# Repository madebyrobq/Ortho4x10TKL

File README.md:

# Ortho 4x10 TKL v0.1

### Summary

An open-source custom mechanical keyboard featuring
* 4x10 ortholinear 'tenkeyless' style layout
* Raspberry Pi RP2040 integrated microcontroller
* USB-C
* Hotswap sockets
* Fully factory-assembled PCBA
* QMK Vial firmware

### Goals

The goals of this project were:
1. Learn how to make a working PCBA mechanical keyboard
2. Keep hardware features to the minimum (no LEDs, OLED, encoders, etc.)
3. Fun and delighful > practical
4. Companion for iPad Mini (6th gen)

### Layout

Spacebar cluster supports 3x1U and 1x3U layouts. Stabilizers are not currently supported but can be substituted with loose switches if desired.

Arrow cluster supports 4 or 6 keys, although the top cases in this repo will cover up 2 of them. Still, the switches are there if you prefer to have them.

### Keymap

This is my keymap, note that with VIAL firmware some setup will be manual in the VIAL application or loaded from a saved layout

```
Default Layer:
┌───────┬───────┬───────┬───────┬───────┬───────┬───────┐┌───────┬───────┬───────┐
│   Q (TAB) W   │   E   │   R   │   T   │   Y   │   U   ││   I   │   O (DEL) P   │
└───────┴───────┴───────┴───────┴───────┴───────┴───────┘├───────┼───────┼───────┤
┌───────┬───────┬───────┬───────┬───────┬───────┬───────┐│   K   │   L (ENT) ;   │
│   A (ESC) S   │   D   │   F   │   G   │   H   │   J   │└───────┴───────┴───────┘
├───────┼───────┼───────┼───────┼───────┼───────┼───────┤┌       ┌───────┐       ┐
│  Z(⇧) │   X   │   C   │   V   │   B   │   N   │  M(⇧) │  PG DN │   Up  │ PG UP
├───────┼───────┼───────┼───────┼───────┼───────┼───────┤┌───────┼───────┼───────┐
│   ⌥   │   ⌘   │         Space         │   ,   │   .   ││  Left │  Down │ Right │
└───────┴───────┴───────┴───────┴───────┴───────┴───────┘└───────┴───────┴───────┘

Raise Layer:
┌───────┬───────┬───────┬───────┬───────┬───────┬───────┐┌───────┬───────┬───────┐
│   1  (`)  2   │   3   │   4   │   -   │   +   │       ││   [   │   ]   |   '   │
└───────┴───────┴───────┴───────┴───────┴───────┴───────┘├───────┼───────┼───────┤
┌───────┬───────┬───────┬───────┬───────┬───────┬───────┐│   (   │   )   |       │
│   4   |   5   │   6   │   0   │   /   │   *   │   =   │└───────┴───────┴───────┘
├───────┼───────┼───────┼───────┼───────┼───────┼───────┤┌       ┌───────┐       ┐
│  7(⇧) │   8   │   9   │   .   │   |   │   &   │   ?   │        │   ⇧   │       
├───────┼───────┼───────┼───────┼───────┼───────┼───────┤┌───────┼───────┼───────┐
│   ⌥   │  0(⌘) │                       │       │       ││   <   │   ⌃   │   >   │
└───────┴───────┴───────┴───────┴───────┴───────┴───────┘└───────┴───────┴───────┘
```

Key Overrides I use:
* `Shift` + `,` = `!`
* `Shift` + `.` = `?`
* `Shift` + `/` = `\`
* `Cmd` + `Q` = `Cmd` + `Tab` (quit too many apps adapting to this layout lol)

### PCB

Version 0.1 - First PCBA ordered from JLCPCB, it works!

### Firmware

Vial firmware is compiled in [here](vial/), along with saved keymaps (including combos and settings that could not be baked into the firmware) which can be loaded from the Vial application.

QMK firmware source will be added soon

### Case & Parts

Can be 3D printed or CNC'd. The 3D printed variants simply have hex holes to fit a standoff, which can be glued in and act as the thread for the screws. The CNC files will work for 3D printing as well if the holes on the top case are tapped manually.

| Part                                      |                          Note                           |
|-------------------------------------------|:-------------------------------------------------------:|
| PCBA                                      |                    [PCB files](PCB/)                    |
| Plate                                     | [Laser Cut Plate](Case/)<br/>1.5mm brass / steel / etc. |
| Top Case                                  |                [Multiple options](Case/)                |
| Bottom Case                               |                  [STL or STEP](Case/)                   |
| Screws                                    |                4x M2.5 10mm counter sunk                |
| Hex standoffs or nuts<br>(if 3D printing) |                       4x M2.5 5mm                       |
| Rubber feet/bumpons                       |                           4x                            |
| Switches and keycaps                      |                      36 to 40 each                      |

## What's Next

I'm quite satisfied with getting this working, and I had to order a minimum of 5 PCBs so I don't plan on making more for a while. But if you find this and use it as an example, here are some ideas of what could be added or improved:
* Layouts
  * Support for more spacebar layouts like 2u in between the existing keys
  * Clip-in stabilizer support
* PCB design
  * Move the USB - since the iPad plugs in on the right it could be nice and compact to put the USB on the right edge of the case
  * Cluster or consolidate the Reset and Boot pins. I was more concerned with finding a place they fit and were easy to route, but it's quite odd especially now that I know you have to either press them both simultaneously or hold Boot while plugging in the USB (which I put on opposite sides).
  * Improve routing and reduce PCB "forehead". But I kind of like the look.
  * Try another MCU. The Raspberry Pi is totally fine, but there are other MCUs that have more packaged features like flash and crystal, so that would be fewer parts to order, and easier to route.
* Other hardware features
  * Add more hardware features like LEDs, ESD, etc.
  * Breakout pins to add hardware features or a daughter board later
* Case
  * Support for more devices
  * Perfect the USB-C cutout
  * Design out of a single piece of aluminum to reduce cost

## Thanks to

For excellent custom keyboard and PCB tutorials (highly recommend starting here if you are interested): [Noah Kiser](https://www.youtube.com/@noahkiser), [Joe Scotto](https://www.youtube.com/@joe_scotto)

For layout inspiration: Zicodia ("LMAO"), tominabox1 and whydobearsxplod ("QAZ"), Jack Humbert ("Planck")

## Disclaimer

**Offered without warranty or liability! Use / modify / order at your own risk. No customer support.**

For a first attempt, and as a hobby project, it turned out quite well! But this was just for fun and not made with the rigor or intent to commercialize it (for now...) so it isn't perfect.

Feel free to use this repository under the license provided. If it helps you make something cool, I would be happy to see it!

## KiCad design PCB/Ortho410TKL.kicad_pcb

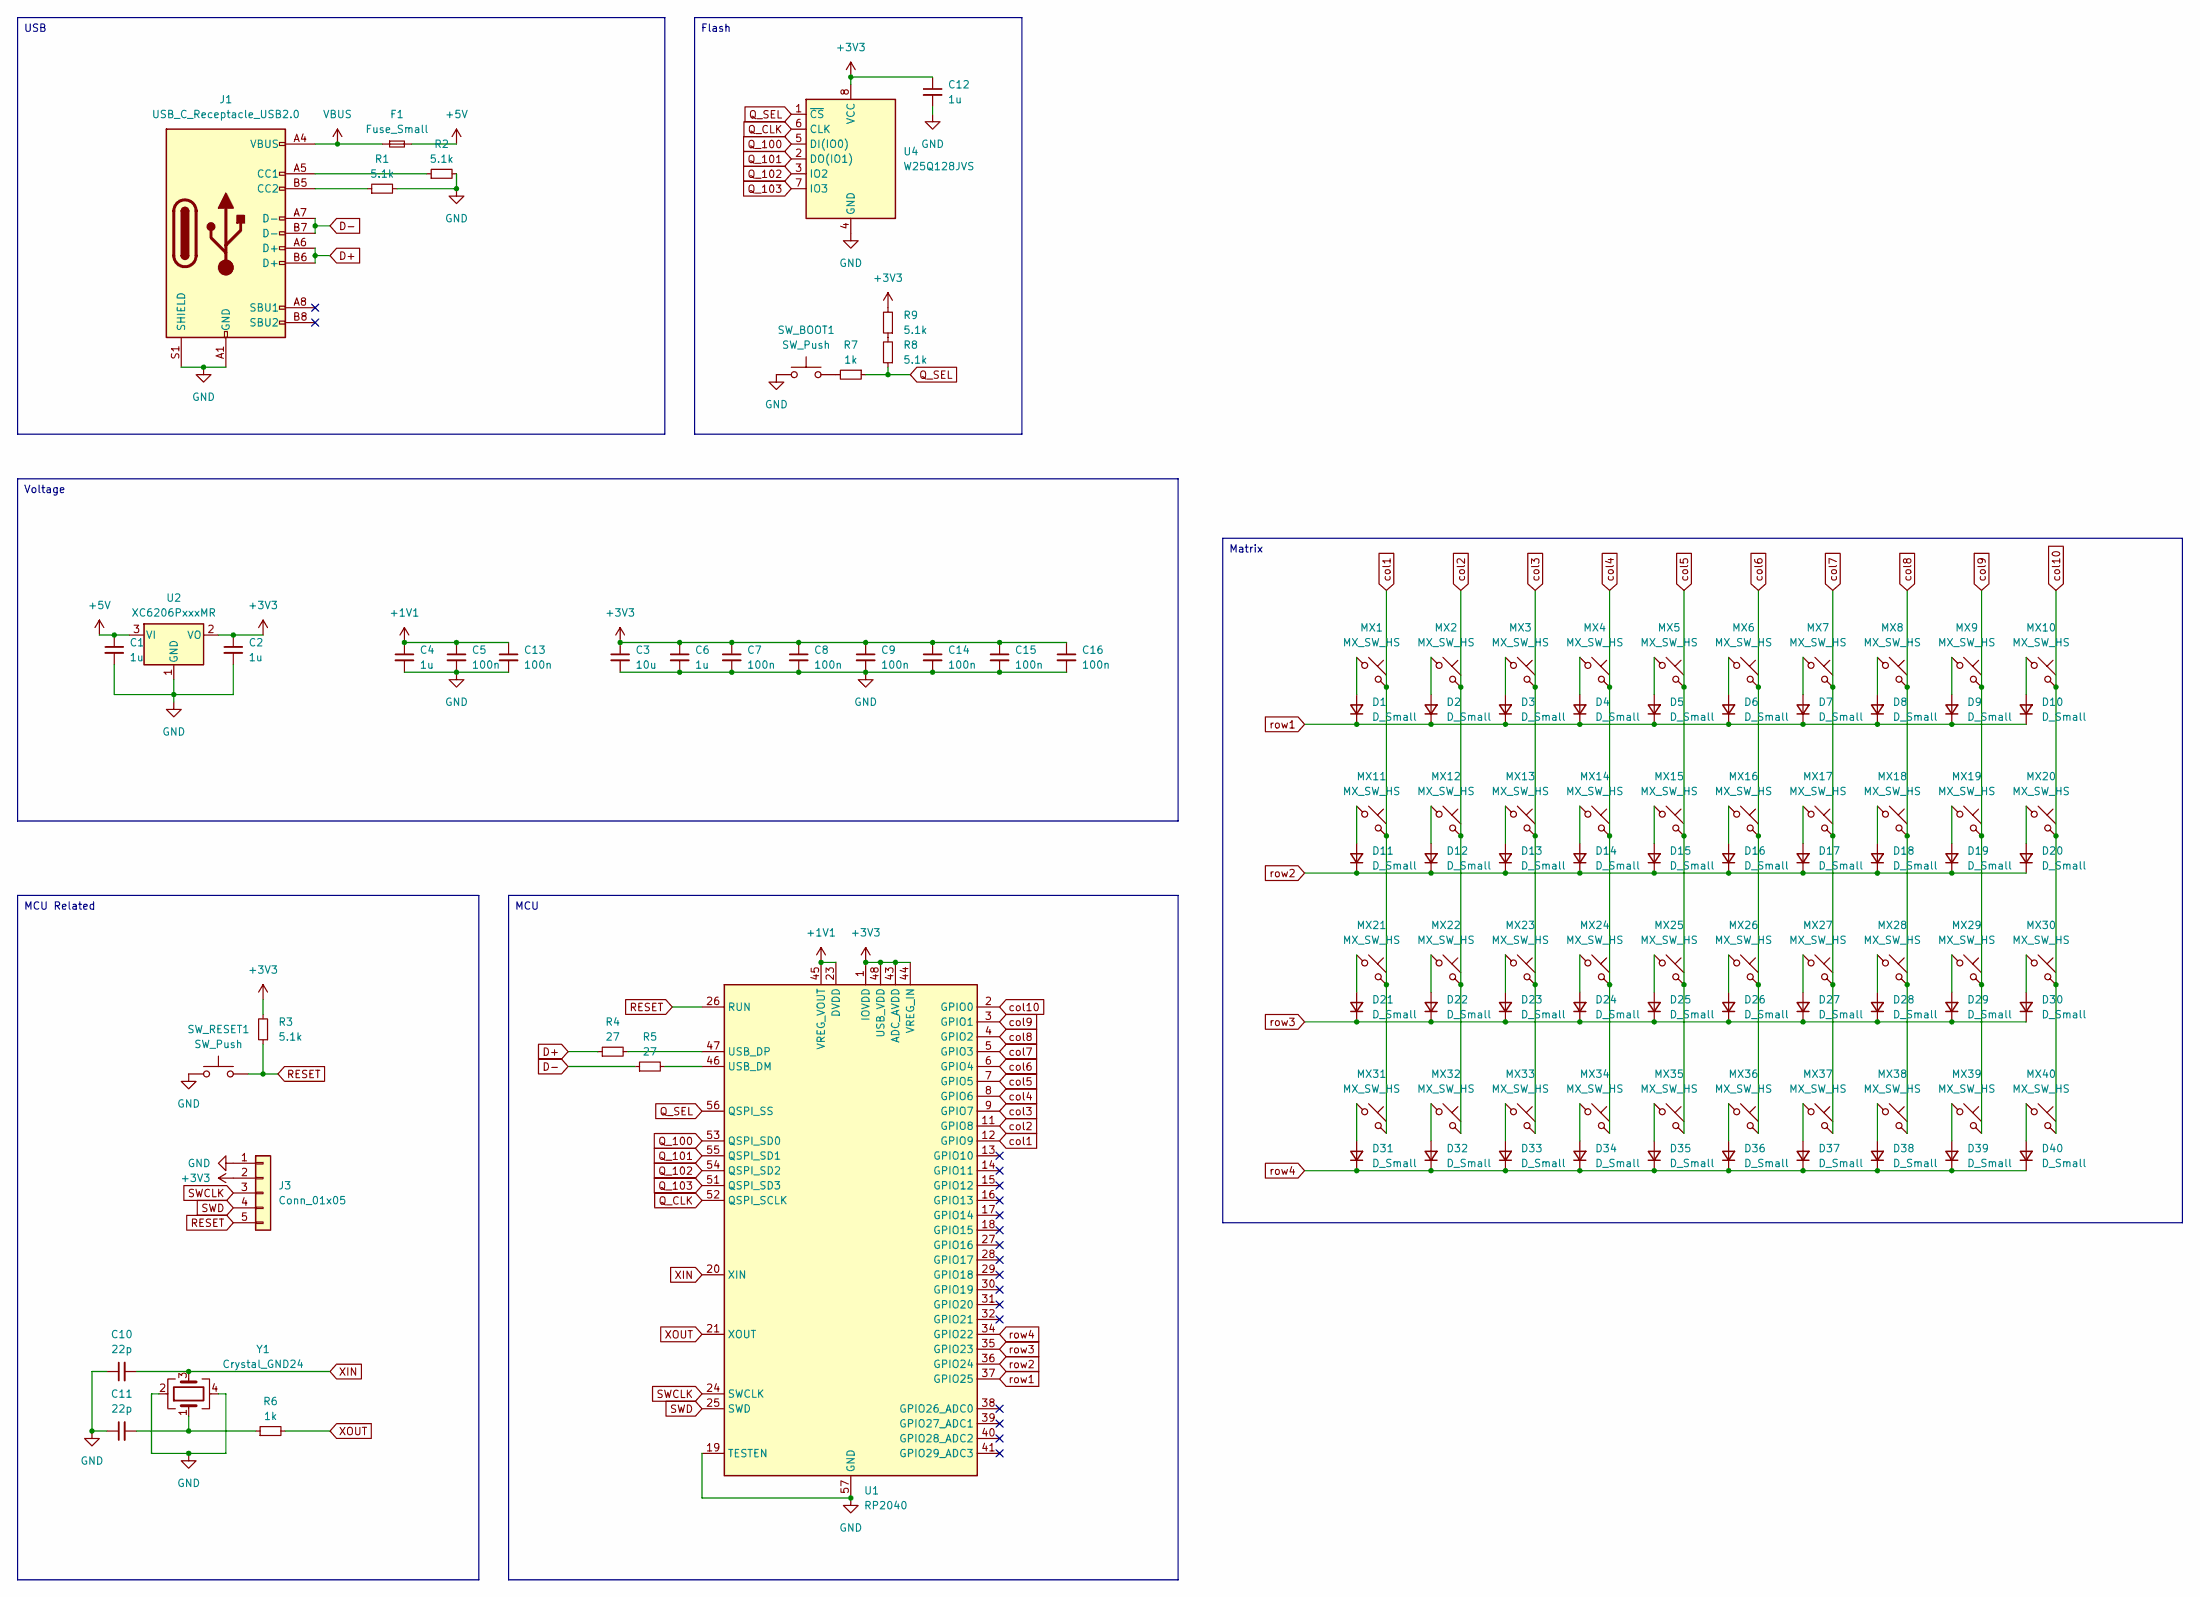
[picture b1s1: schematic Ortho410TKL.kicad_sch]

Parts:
C1, C2, C4, C6, C12: 1u; C_0402_1005Metric
C3: 10u; C_0603_1608Metric
C5, C7, C8, C9, C13, C14, C15, C16: 100n; C_0402_1005Metric
C10, C11: 22p; C_0402_1005Metric
D1, D2, D3, D4, D5, D6, D7, D8, D9, D10, D11, D12, D13, D14, D15, D16, D17, D18, D19, D20, D21, D22, D23, D24, D25, D26, D27, D28, D29, D30, D31, D32, D33, D34, D35, D36, D37, D38, D39, D40: D_Small; D_SOD-123
F1: Fuse_Small; Fuse_1206_3216Metric
J1: USB_C_Receptacle_USB2.0; USB_C_Receptacle_HRO_TYPE-C-31-M-12
J3: Conn_01x05; PinHeader_1x05_P2.54mm_Vertical
MX1, MX2, MX3, MX4, MX5, MX6, MX7, MX8, MX9, MX10, MX11, MX12, MX13, MX14, MX15, MX16, MX17, MX18, MX19, MX20, MX21, MX22, MX23, MX24, MX25, MX26, MX27, MX28, MX29, MX30, MX31, MX32, MX33, MX34, MX35, MX36, MX37, MX38, MX39, MX40: MX_SW_HS; SW_MX_HS_1u
R1, R2, R3, R8, R9: 5.1k; R_0402_1005Metric
R4, R5: 27; R_0402_1005Metric
R6, R7: 1k; R_0402_1005Metric
SW_BOOT1: SW_Push; SW_SPST_TL3342
SW_RESET1: SW_Push; SW_SPST_TL3342
U1: RP2040; QFN-56-1EP_7x7mm_P0.4mm_EP3.2x3.2mm
U2: XC6206PxxxMR; SOT-23-3
U4: W25Q128JVS; SOIC-8_5.23x5.23mm_P1.27mm
Y1: Crystal_GND24; Crystal_SMD_3225-4Pin_3.2x2.5mm

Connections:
+1V1: C4.1, C5.1, C13.1, U1.23 (DVDD), U1.45 (VREG_VOUT), U1.50 (DVDD)
+3V3: C2.1, C3.1, C6.1, C7.1, C8.1, C9.1, C12.1, C14.1, C15.1, C16.1, J3.2, R3.2, R9.2, U1.1 (IOVDD), U1.10 (IOVDD), U1.22 (IOVDD), U1.33 (IOVDD), U1.42 (IOVDD), U1.43 (ADC_AVDD), U1.44 (VREG_IN), U1.48 (USB_VDD), U1.49 (IOVDD), U2.2 (VO), U4.8 (VCC)
+5V: C1.1, F1.2, U2.3 (VI)
D+: J1.A6 (D+), J1.B6 (D+), R4.1
D-: J1.A7 (D-), J1.B7 (D-), R5.1
GND: C1.2, C2.2, C3.2, C4.2, C5.2, C6.2, C7.2, C8.2, C9.2, C10.1, C11.1, C12.2, C13.2, C14.2, C15.2, C16.2, J1.A1 (GND), J1.A12 (GND), J1.B1 (GND), J1.B12 (GND), J1.S1 (SHIELD), J3.1, R1.2, R2.2, SW_BOOT1.1, SW_RESET1.1, U1.19 (TESTEN), U1.57 (GND), U2.1 (GND), U4.4 (GND), Y1.2, Y1.4
unnamed: C11.2, R6.1, Y1.1
unnamed: D1.2 (A), MX1.1
unnamed: D2.2 (A), MX2.1
unnamed: D3.2 (A), MX3.1
unnamed: D4.2 (A), MX4.1
unnamed: D5.2 (A), MX5.1
unnamed: D6.2 (A), MX6.1
unnamed: D7.2 (A), MX7.1
unnamed: D8.2 (A), MX8.1
unnamed: D9.2 (A), MX9.1
unnamed: D10.2 (A), MX10.1
unnamed: D11.2 (A), MX11.1
unnamed: D12.2 (A), MX12.1
unnamed: D13.2 (A), MX13.1
unnamed: D14.2 (A), MX14.1
unnamed: D15.2 (A), MX15.1
unnamed: D16.2 (A), MX16.1
unnamed: D17.2 (A), MX17.1
unnamed: D18.2 (A), MX18.1
unnamed: D19.2 (A), MX19.1
unnamed: D20.2 (A), MX20.1
unnamed: D21.2 (A), MX21.1
unnamed: D22.2 (A), MX22.1
unnamed: D23.2 (A), MX23.1
unnamed: D24.2 (A), MX24.1
unnamed: D25.2 (A), MX25.1
unnamed: D26.2 (A), MX26.1
unnamed: D27.2 (A), MX27.1
unnamed: D28.2 (A), MX28.1
unnamed: D29.2 (A), MX29.1
unnamed: D30.2 (A), MX30.1
unnamed: D31.2 (A), MX31.1
unnamed: D32.2 (A), MX32.1
unnamed: D33.2 (A), MX33.1
unnamed: D34.2 (A), MX34.1
unnamed: D35.2 (A), MX35.1
unnamed: D36.2 (A), MX36.1
unnamed: D37.2 (A), MX37.1
unnamed: D38.2 (A), MX38.1
unnamed: D39.2 (A), MX39.1
unnamed: D40.2 (A), MX40.1
unnamed: J1.A5 (CC1), R2.1
unnamed: J1.B5 (CC2), R1.1
unnamed: R7.2, SW_BOOT1.2
unnamed: R8.2, R9.1
unnamed: R5.2, U1.46 (USB_DM)
unnamed: R4.2, U1.47 (USB_DP)
Q_100: U1.53 (QSPI_SD0), U4.5 (DI(IO0))
Q_101: U1.55 (QSPI_SD1), U4.2 (DO(IO1))
Q_102: U1.54 (QSPI_SD2), U4.3 (IO2)
Q_103: U1.51 (QSPI_SD3), U4.7 (IO3)
Q_CLK: U1.52 (QSPI_SCLK), U4.6 (CLK)
Q_SEL: R7.1, R8.1, U1.56 (QSPI_SS), U4.1 (~CS)
RESET: J3.5, R3.1, SW_RESET1.2, U1.26 (RUN)
SWCLK: J3.3, U1.24 (SWCLK)
SWD: J3.4, U1.25 (SWD)
VBUS: F1.1, J1.A4 (VBUS), J1.A9 (VBUS), J1.B4 (VBUS), J1.B9 (VBUS)
XIN: C10.2, U1.20 (XIN), Y1.3
XOUT: R6.2, U1.21 (XOUT)
col1: MX1.2, MX11.2, MX21.2, MX31.2, U1.12 (GPIO9)
col2: MX2.2, MX12.2, MX22.2, MX32.2, U1.11 (GPIO8)
col3: MX3.2, MX13.2, MX23.2, MX33.2, U1.9 (GPIO7)
col4: MX4.2, MX14.2, MX24.2, MX34.2, U1.8 (GPIO6)
col5: MX5.2, MX15.2, MX25.2, MX35.2, U1.7 (GPIO5)
col6: MX6.2, MX16.2, MX26.2, MX36.2, U1.6 (GPIO4)
col7: MX7.2, MX17.2, MX27.2, MX37.2, U1.5 (GPIO3)
col8: MX8.2, MX18.2, MX28.2, MX38.2, U1.4 (GPIO2)
col9: MX9.2, MX19.2, MX29.2, MX39.2, U1.3 (GPIO1)
col10: MX10.2, MX20.2, MX30.2, MX40.2, U1.2 (GPIO0)
row1: D1.1 (K), D2.1 (K), D3.1 (K), D4.1 (K), D5.1 (K), D6.1 (K), D7.1 (K), D8.1 (K), D9.1 (K), D10.1 (K), U1.37 (GPIO25)
row2: D11.1 (K), D12.1 (K), D13.1 (K), D14.1 (K), D15.1 (K), D16.1 (K), D17.1 (K), D18.1 (K), D19.1 (K), D20.1 (K), U1.36 (GPIO24)
row3: D21.1 (K), D22.1 (K), D23.1 (K), D24.1 (K), D25.1 (K), D26.1 (K), D27.1 (K), D28.1 (K), D29.1 (K), D30.1 (K), U1.35 (GPIO23)
row4: D31.1 (K), D32.1 (K), D33.1 (K), D34.1 (K), D35.1 (K), D36.1 (K), D37.1 (K), D38.1 (K), D39.1 (K), D40.1 (K), U1.34 (GPIO22)

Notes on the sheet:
Flash
MCU
Matrix
Voltage
MCU Related
USB

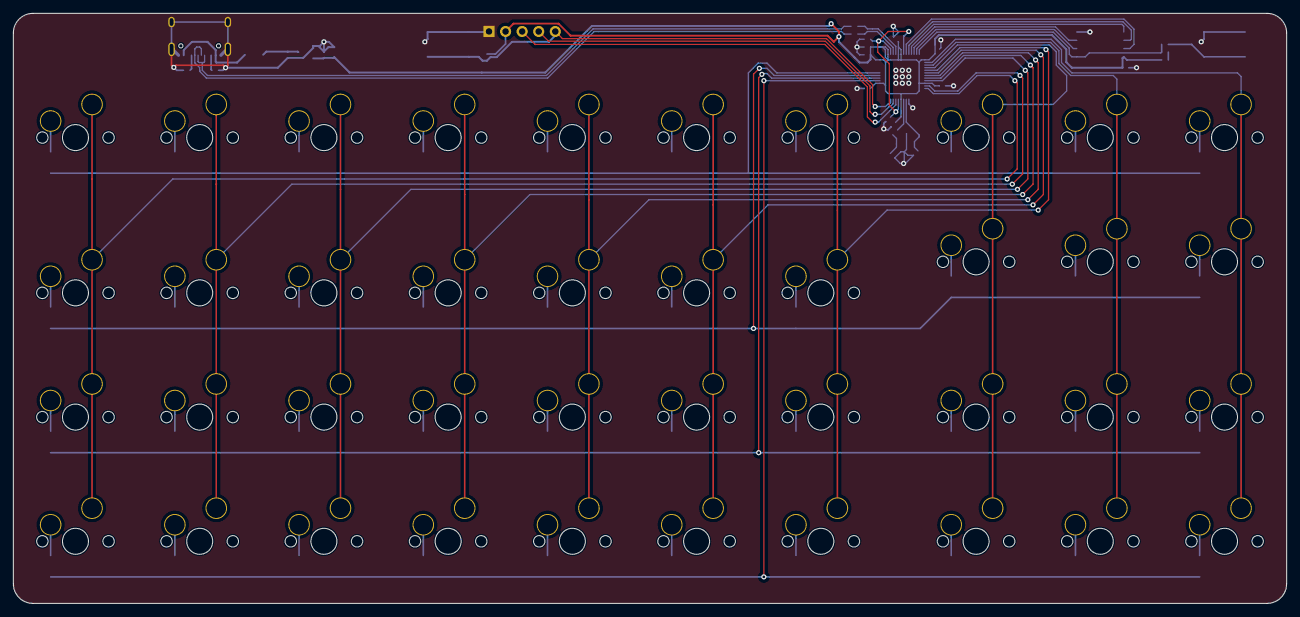
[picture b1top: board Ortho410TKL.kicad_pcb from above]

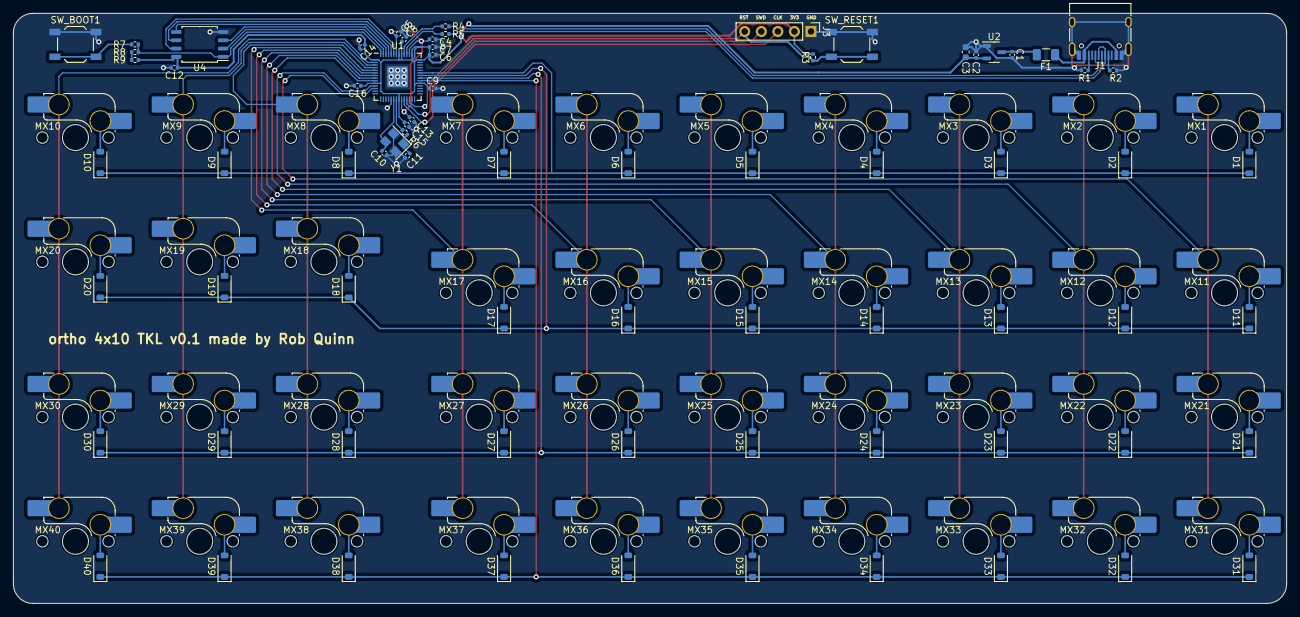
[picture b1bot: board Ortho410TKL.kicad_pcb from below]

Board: 2 copper layers, 195.3 x 90.5 mm, 114 parts (114 on the bottom side), 79 nets.

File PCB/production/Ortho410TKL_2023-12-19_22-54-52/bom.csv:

Designator,Footprint,Quantity,Value,LCSC Part #
"C1, C12, C2, C4, C6",0402,5,1u,
"C10, C11",0402,2,22p,
"C13, C14, C15, C16, C5, C7, C8, C9",0402,8,100n,
C3,0603,1,10u,
"D1, D10, D11, D12, D13, D14, D15, D16, D17, D18, D19, D2, D20, D21, D22, D23, D24, D25, D26, D27, D28, D29, D3, D30, D31, D32, D33, D34, D35, D36, D37, D38, D39, D4, D40, D5, D6, D7, D8, D9",D_SOD-123,40,D_Small,
F1,1206,1,Fuse_Small,
J1,USB_C_Receptacle_HRO_TYPE-C-31-M-12,1,USB_C_Receptacle_USB2.0,
J3,PinHeader_1x05_P2.54mm_Vertical,1,Conn_01x05,
"MX1, MX10, MX11, MX12, MX13, MX14, MX15, MX16, MX17, MX18, MX19, MX2, MX20, MX21, MX22, MX23, MX24, MX25, MX26, MX27, MX28, MX29, MX3, MX30, MX31, MX32, MX33, MX34, MX35, MX36, MX37, MX38, MX39, MX4, MX40, MX5, MX6, MX7, MX8, MX9",SW_MX_HS_1u,40,MX_SW_HS,
"R1, R2, R3, R8, R9",0402,5,5.1k,
"R4, R5",0402,2,27,
"R6, R7",0402,2,1k,
"SW_BOOT1, SW_RESET1",SW_SPST_TL3342,2,SW_Push,
U1,QFN-56-1EP_7x7mm_P0.4mm_EP3.2x3.2mm,1,RP2040,
U2,SOT-23-3,1,XC6206PxxxMR,
U4,SOIC-8_5.23x5.23mm_P1.27mm,1,W25Q128JVS,
Y1,Crystal_SMD_3225-4Pin_3.2x2.5mm,1,Crystal_GND24,

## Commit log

2023-12-30 initial commit of pcb files
2023-12-30 Update LICENSE
2023-12-30 vial firmware
2024-08-24 adding saved vial keymaps
2024-08-24 updated , and . layout
2024-08-28 start of case files
2024-09-01 updated saved keymaps
2024-10-26 cnc, photo
2025-03-31 updated vial firmware to 0.7.2 - fixes tap hold!
